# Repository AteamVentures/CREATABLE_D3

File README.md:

# CREATABLE_D3
The Perfect 3D Printer for Beginners, Educators and Experts.
[creatablelabs.com](http://creatablelabs.com/)

## Open Source Hardware
This product is certified open source hardware. 
[https://certification.oshwa.org/kr000001.html](https://certification.oshwa.org/kr000001.html)

#### Folder Description
 - Hardware : Mainboard, OLED board, Heat bed circuit board and PCB file (The mainboard is working with Allegro of Cadence and the rest is working with Eagle CAD)
 - Firmware : Mainboard firmware [Download](https://github.com/AteamVentures/CREATABLE_D3/raw/master/Firmware/D3_Firmware.zip)  
	1. Connect the printer and computer with the USB cable.
	2. Unzip the file you received from the link above.
	3. Run Cue and execute Machine> Install Custom Firmware ... from the main menu.
	4. Select the hex file from step 2 and click Open.
	5. Wait for uploading to finish.
	6. After completing the upload, operate the printer's menu to execute INFO / SETTINGS> RESTORE DEFAULT.
	7. Execute the leveling and filament insertion according to the first run instructions. If you have already done so, continue to press the button without further action.
	8. Execute INFO / SETTINGS> FIRMWARE VERSION to check the version information.

 - stk500v2 : This it the ATmega2560 bootloader of main board.

#### Cura CREATABLE Edition

- To use the printer, a slicing process is required to convert model files (stl, obj, etc.) to Gcode. To do this, we offer Cura CREATABLE Edition, a slicing software.
- Information on the Cura CREATABLE Edition can be found at the following link.
- [Cura CREATABLE Edition](https://github.com/AteamVentures/CuraCreatableEdition)

#### Folder Description
 -  Hardware: Mainboard, OLED board, Heat bed circuit board and PCB file (The mainboard is working with Cadence's Allegro and the rest with Eagle CAD)
 - Firmware : Mainboard firmware [Download](https://github.com/AteamVentures/CREATABLE_D3/raw/master/Firmware/D3_Firmware.zip)  
	#### How to update firmare
	1. Connect the printer and computer with a USB cable.
	2. Unzip the file you received from the link above.
	3. Execute Cura and run Machine> Install Custom Firmware ... from the main menu.
	4. Select the hex file from step 2 and click "Open".
	5. Wait for uploading to finish.
	6. After completing the upload, operate the printer's menu to execute INFO / SETTINGS> RESTORE DEFAULT.
	7. Execute leveling and filament insertion according to "First run" instructions. If you have already done so, continue to press the button without further action.
	8. Execute INFO / SETTINGS> FIRMWARE VERSION to check the version information.
	- stk500v2 : 메인 보드 ATmega2560 bootloader

#### Differences from Creatable D2 in H/W

- Using Silab's CP2104 for USB connection
- Motor driver A4988 is onboard.
- OLED board: Integrate 2 boards into one board
- Heat bed: Adjusts the resistance value so that it is heated quickly.

#### Cura CREATABLE Edition

- To use the printer, a slicing process is required to convert model files (stl, obj, etc.) into Gcode. To do this, we offer Cura CREATABLE Edition (Cutomized Cura).
- Information about the Cura CREATABLE Edition can be found at the following link.
- [Cura CREATABLE Edition Link](https://github.com/AteamVentures/CuraCreatableEdition)

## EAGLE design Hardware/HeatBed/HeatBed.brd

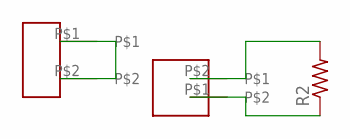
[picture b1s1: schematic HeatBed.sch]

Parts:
R2: R-US_R0402; R0402
U$2: SMD_WAFER_2; SMD_WAFER_02
U$3: SMD_TERMINAL_2; SMD_5MM_2

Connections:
unnamed: R2.2, U$2.P$2
unnamed: R2.1, U$2.P$1
unnamed: U$3.P$1, U$3.P$2

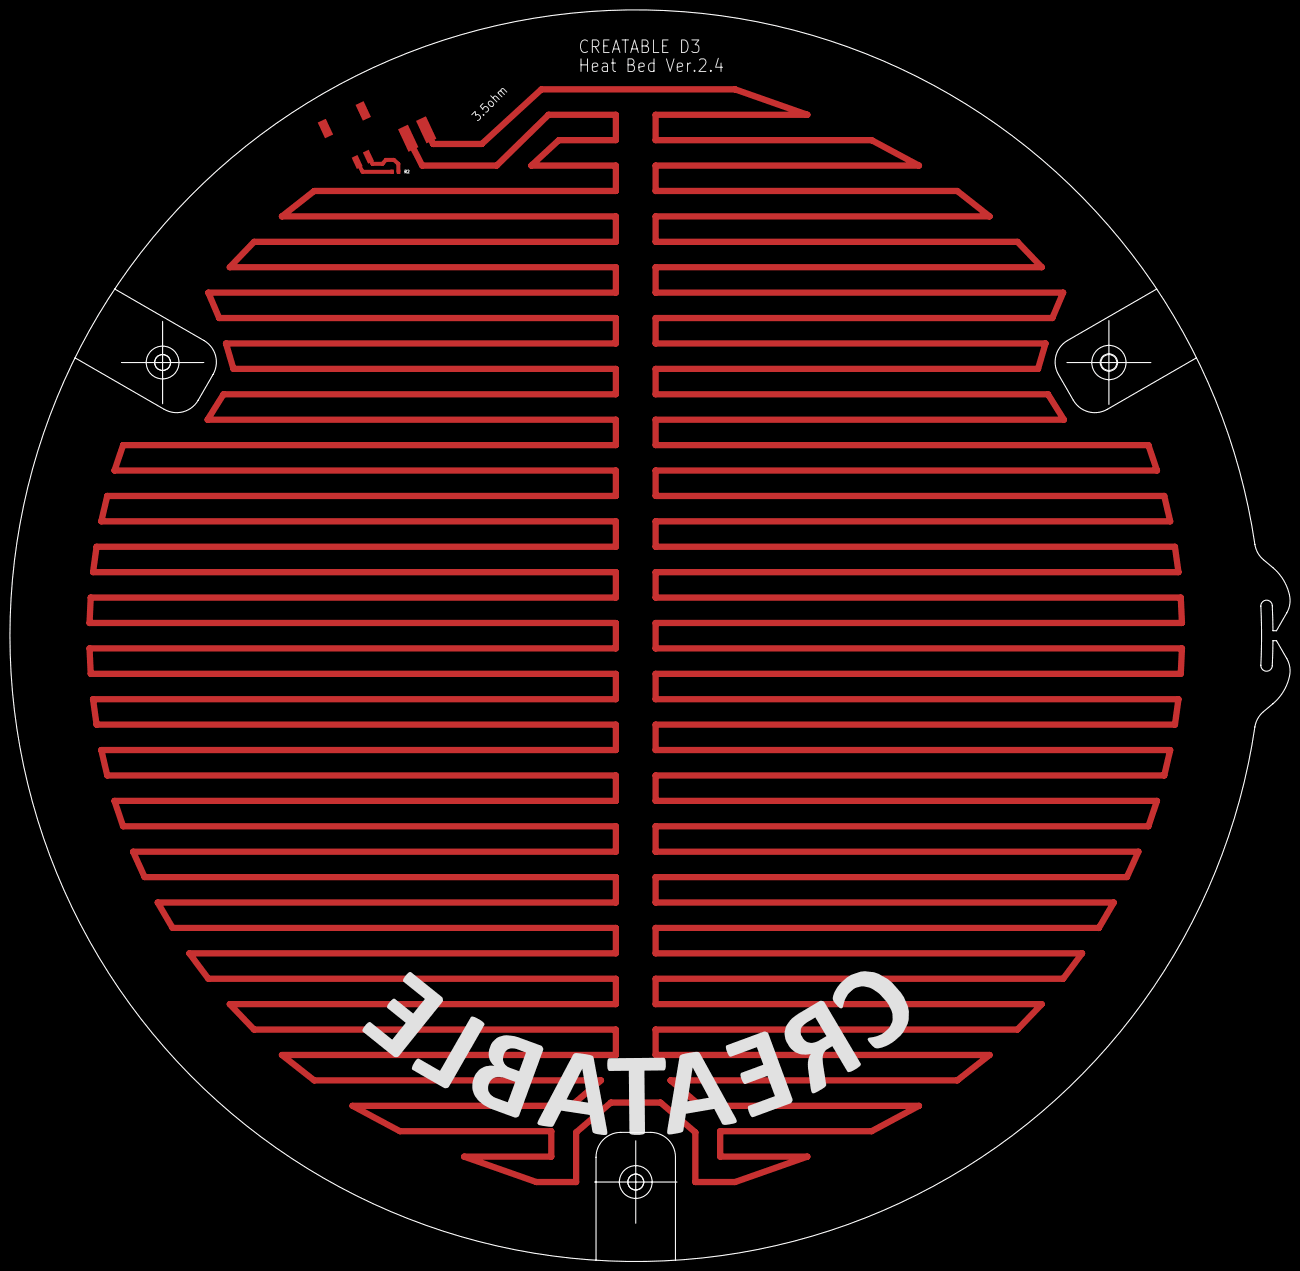
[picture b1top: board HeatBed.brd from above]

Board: 2 copper layers, 257.7 x 252.0 mm, 5 parts (1 on the bottom side), 3 nets.

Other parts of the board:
U$1: HEAT_BED2.3(R126_T2.3)
U$4: CREATABLE_WORD

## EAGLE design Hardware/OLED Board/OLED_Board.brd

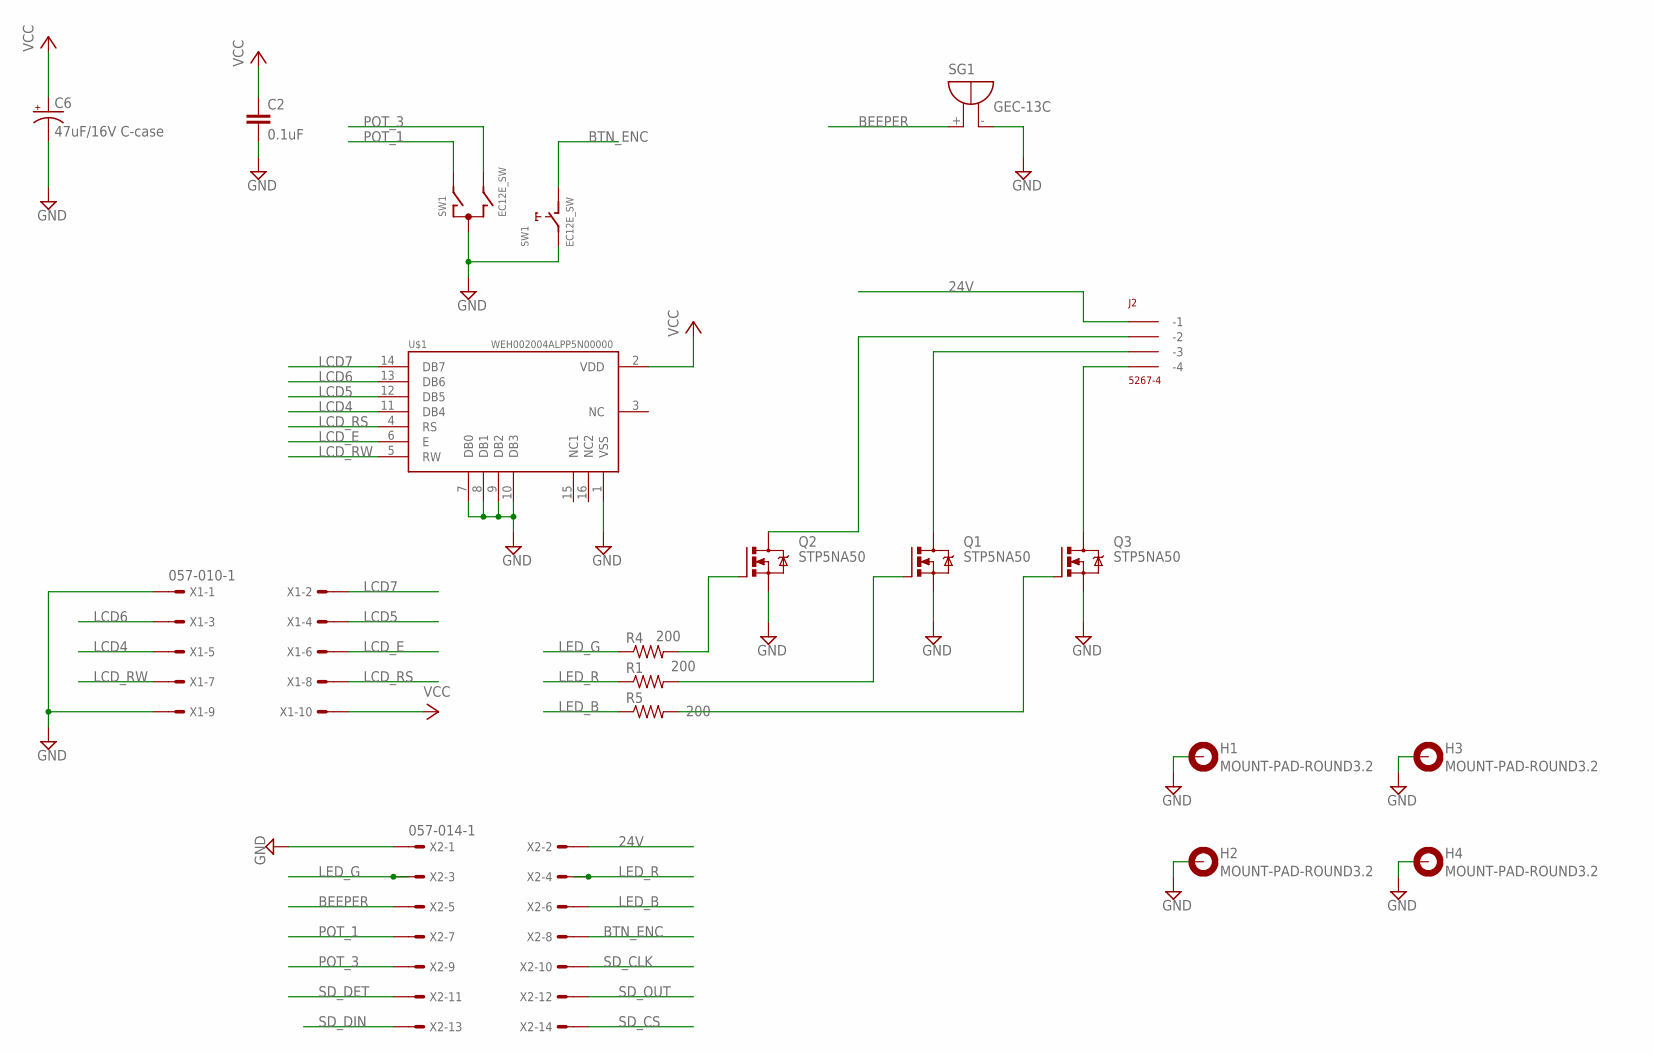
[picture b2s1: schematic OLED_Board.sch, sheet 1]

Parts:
C2: 0.1uF; C0805
C6: 47uF/16V C-case; EIA6032
H1, H2, H3, H4: MOUNT-PAD-ROUND3.2; 3,2-PAD
J2: 5267-4
Q1, Q2, Q3: STP5NA50; TO220BV
R1, R4, R5: 200; R2012
SG1: GEC-13C; F/TMB
SW1: EC12E_SW; ALPS_EC12E_SW
U$1: OLED; WEH002004ALPP5N00000
X1: 057-010-1
X2: 057-014-1

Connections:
24V: J2.P$1 (-1), X2.2
BEEPER: SG1.+, X2.5
BTN_ENC: SW1.D (1), X2.8
GND: C2.2, C6.P$2 (-), H1.B3,2, H2.B3,2, H3.B3,2, H4.B3,2, Q1.S, Q2.S, Q3.S, SG1.-, SW1.C, SW1.E (2), U$1.1 (VSS), U$1.7 (DB0), U$1.8 (DB1), U$1.9 (DB2), U$1.10 (DB3), X1.1, X1.9, X2.1; also elsewhere on the board
LCD4: U$1.11 (DB4), X1.5
LCD5: U$1.12 (DB5), X1.4
LCD6: U$1.13 (DB6), X1.3
LCD7: U$1.14 (DB7), X1.2
LCD_E: U$1.6 (E), X1.6
LCD_RS: U$1.4 (RS), X1.8
LCD_RW: U$1.5 (RW), X1.7
LED_B: R5.1, X2.6
LED_G: R4.1, X2.3
LED_R: R1.1, X2.4
unnamed: Q2.G, R4.2
unnamed: Q1.G, R1.2
unnamed: Q3.G, R5.2
unnamed: J2.P$2 (-2), Q2.D
unnamed: J2.P$3 (-3), Q1.D
unnamed: J2.P$4 (-4), Q3.D
POT_1: SW1.A, X2.7
POT_3: SW1.B, X2.9
SD_CLK: X2.10; also elsewhere on the board
SD_CS: X2.14; also elsewhere on the board
SD_DET: X2.11; also elsewhere on the board
SD_DIN: X2.13; also elsewhere on the board
SD_OUT: X2.12; also elsewhere on the board
VCC: C2.1, C6.P$1 (+), U$1.2 (VDD), X1.10; also elsewhere on the board

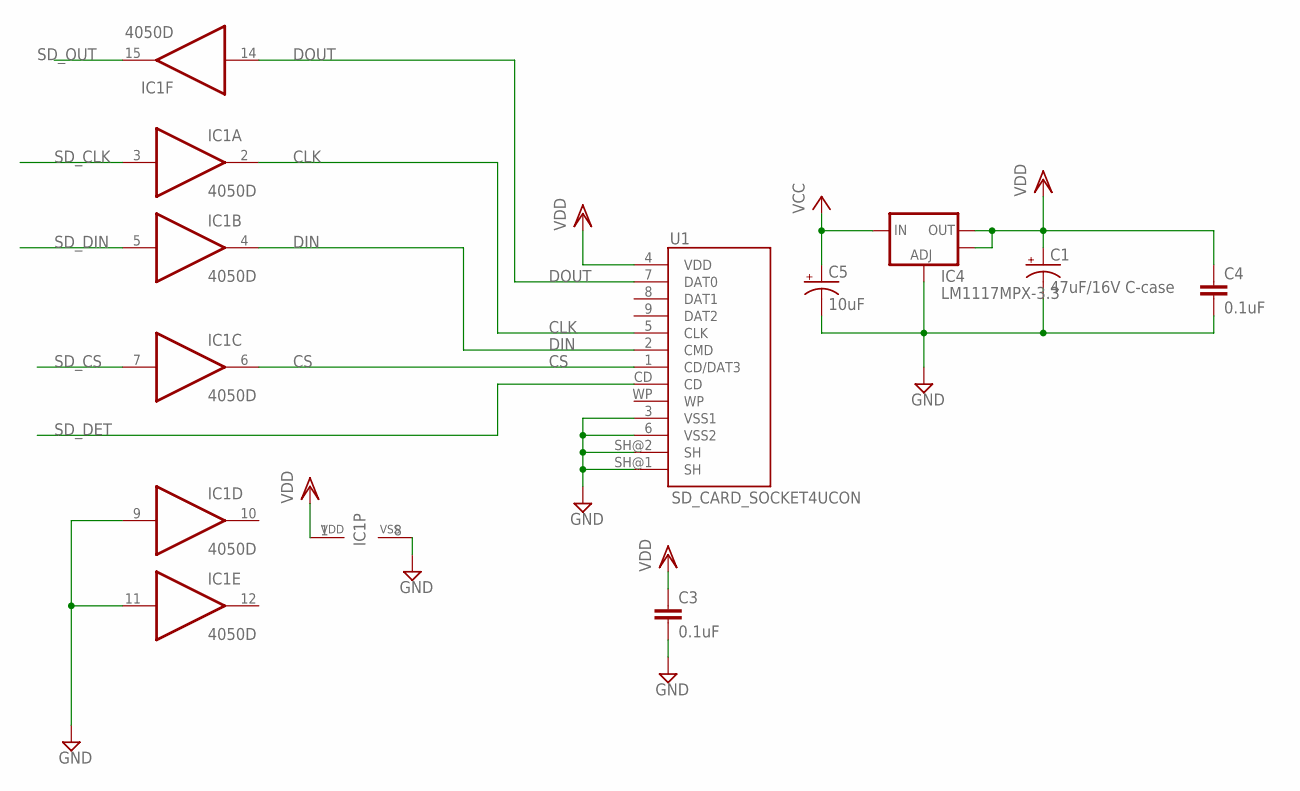
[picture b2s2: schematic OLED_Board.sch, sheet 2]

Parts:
C1: 47uF/16V C-case; EIA6032
C3, C4: 0.1uF; C0805
C5: 10uF; CT3216
IC1: 4050D; SO16
IC4: LM1117MPX-3.3; SOT223
U1: SD_CARD_SOCKET4UCON; SDCARD_4UCONN

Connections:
CLK: IC1.2 (O), U1.5 (CLK)
CS: IC1.6 (O), U1.1 (CD/DAT3)
DIN: IC1.4 (O), U1.2 (CMD)
DOUT: IC1.14 (I), U1.7 (DAT0)
GND: C1.P$2 (-), C3.2, C4.2, C5.-, IC1.8 (VSS), IC1.9 (I), IC1.11 (I), IC4.1 (ADJ), U1.3 (VSS1), U1.6 (VSS2), U1.SH@1 (SH), U1.SH@2 (SH); also elsewhere on the board
SD_CLK: IC1.3 (I); also elsewhere on the board
SD_CS: IC1.7 (I); also elsewhere on the board
SD_DET: U1.CD; also elsewhere on the board
SD_DIN: IC1.5 (I); also elsewhere on the board
SD_OUT: IC1.15 (O); also elsewhere on the board
VCC: C5.+, IC4.3 (IN); also elsewhere on the board
VDD: C1.P$1 (+), C3.1, C4.1, IC1.1 (VDD), IC4.2 (OUT), IC4.4 (OUT), U1.4 (VDD)

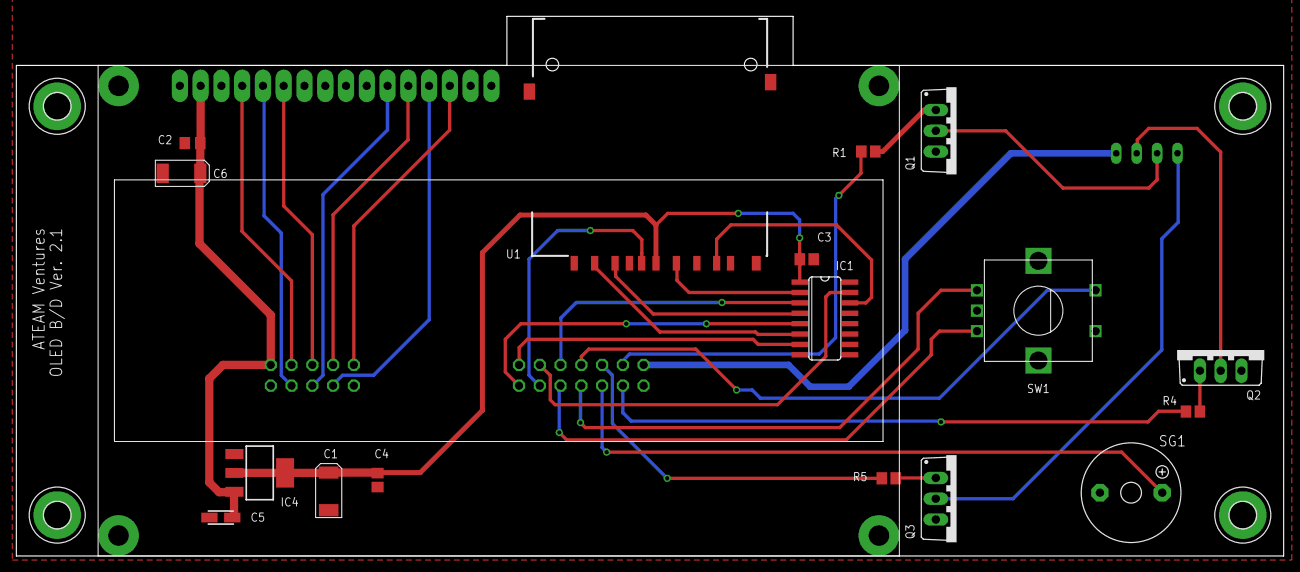
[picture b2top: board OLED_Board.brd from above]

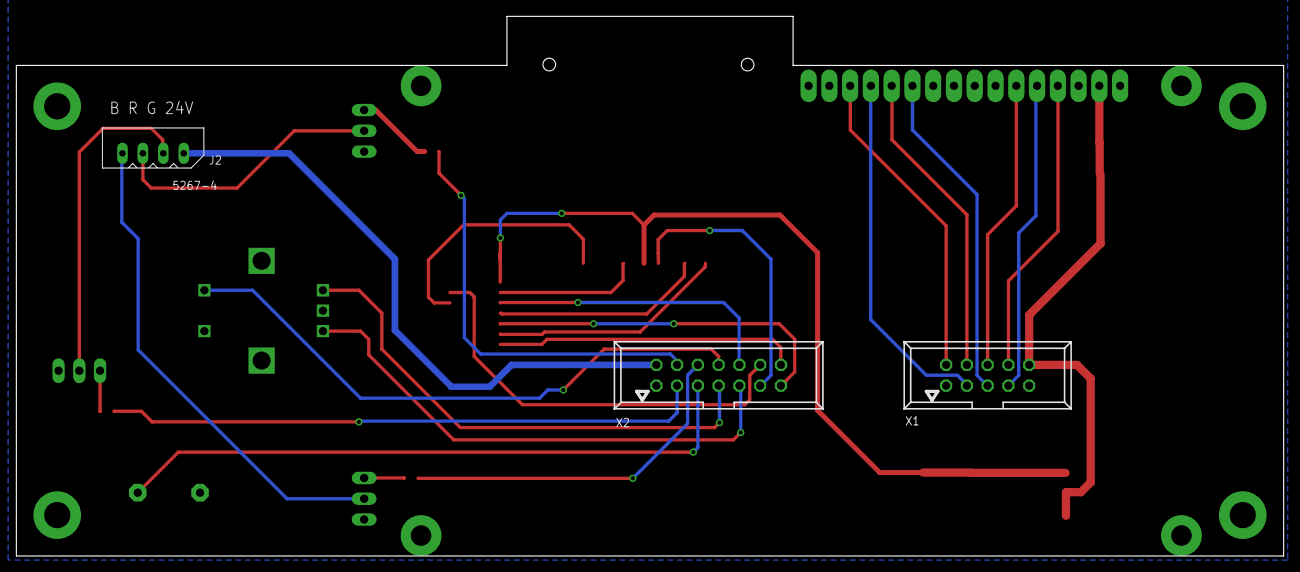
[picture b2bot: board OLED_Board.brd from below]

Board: 2 copper layers, 155.0 x 66.0 mm, 25 parts (3 on the bottom side), 33 nets.

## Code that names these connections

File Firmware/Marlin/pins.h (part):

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    //#define TX_ENABLE_PIN       12
    //#define RX_ENABLE_PIN       13

    #define BEEPER -1
    #define SDCARDDETECT -1
    #define SUICIDE_PIN -1    //has to be defined; otherwise Power_off doesn't work

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     //buttons are directly attached
    #define BTN_EN1 11
    #define BTN_EN2 10
    #define BTN_ENC 12  //the click

#endif

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    #define SDSS               25//53
    #define LED_PIN            13

    #define BEEPER             33

  #else

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  #endif

  #if MOTHERBOARD == 68
    #define BEEPER 33
  #endif

  #ifdef TEMP_STAT_LEDS
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      #define LCD_PINS_D7 29

      #ifdef REPRAP_DISCOUNT_SMART_CONTROLLER
        #define BEEPER 37

        #define BTN_EN1 31
        #define BTN_EN2 33
        #define BTN_ENC 35

        #define SDCARDDETECT 49
      #elif defined(LCD_I2C_PANELOLU2)
        #define BTN_EN1 47  //reverse if the encoder turns the wrong way.
        #define BTN_EN2 43
        #define BTN_ENC 32
        #define SDSS 53
        #define SDCARDDETECT -1
        #define KILL_PIN 41
      #elif defined(LCD_I2C_VIKI)
        #define BTN_EN1 22  //reverse if the encoder turns the wrong way.
        #define BTN_EN2 7
        #define BTN_ENC -1
        #define SDSS 53
        #define SDCARDDETECT 49
      #else
        //arduino pin which triggers an piezzo beeper
        #define BEEPER 33  // Beeper on AUX-4

        //buttons are directly attached using AUX-2
        #ifdef REPRAPWORLD_KEYPAD
          #define BTN_EN1 64 // encoder
          #define BTN_EN2 59 // encoder
          #define BTN_ENC 63 // enter button
          #define SHIFT_OUT 40 // shift register
          #define SHIFT_CLK 44 // shift register
          #define SHIFT_LD 42 // shift register
        #else
          #define BTN_EN1 37
          #define BTN_EN2 35
          #define BTN_ENC 31  //the click
        #endif

        #ifdef G3D_PANEL
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      #endif

      #if MOTHERBOARD == 77
        #define BEEPER -1

        #define LCD_PINS_RS 27
        #define LCD_PINS_ENABLE 29
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       //buttons
       #define BTN_EN1 16
       #define BTN_EN2 17
       #define BTN_ENC 23 //the click

    #endif
    #else //old style panel with shift register
      //arduino pin witch triggers an piezzo beeper
      #define BEEPER 33		//No Beeper added

      //buttons are attached to a shift register
	// Not wired this yet
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#define TEMP_2_PIN         1 	//ANALOG NUMBERING
#define TEMP_BED_PIN       0	//ANALOG NUMBERING

#define BEEPER 		         36

#define KILL_PIN           -1

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
  #define BTN_EN1          14
  #define BTN_EN2          39
  #define BTN_ENC          15  //the click

  #define BLEN_C           2
  #define BLEN_B           1
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 #ifdef ULTRA_LCD
   #ifdef NEWPANEL
     //we have no buzzer installed
     #define BEEPER -1
     //LCD Pins
     #ifdef DOGLCD
       // Pins for DOGM SPI LCD Support
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     #define BTN_EN2 10
     #ifdef LCD_I2C_PANELOLU2
       #ifdef MELZI
         #define BTN_ENC 29 //the click switch
         #define SDSS 30 //to use the SD card reader on the Panelolu2 rather than the melzi board
       #else
         #define BTN_ENC 30 //the click switch
       #endif
     #else
       #define BTN_ENC 16  //the click switch
     #endif //Panelolu2
     //not connected to a pin
     #define SDCARDDETECT -1
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 #endif //Ultipanel

 #ifdef MAKRPANEL
     #define BEEPER 29
     // Pins for DOGM SPI LCD Support
     #define DOGLCD_A0  30
     #define DOGLCD_CS  17
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     //The encoder and click button
     #define BTN_EN1 11
     #define BTN_EN2 10
     #define BTN_ENC 16  //the click switch
     //not connected to a pin
     #define SDCARDDETECT -1
 #endif //Makrpanel
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#ifdef ULTRA_LCD

  #ifdef NEWPANEL
  //arduino pin witch triggers an piezzo beeper
    #define BEEPER 18

    #define LCD_PINS_RS 20
    #define LCD_PINS_ENABLE 17
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    //buttons are directly attached
    #define BTN_EN1 40
    #define BTN_EN2 42
    #define BTN_ENC 19  //the click

    #define SDCARDDETECT 38

  #else //old style panel with shift register
    //arduino pin witch triggers an piezzo beeper
    #define BEEPER 18

    //buttons are attached to a shift register
    #define SHIFT_CLK 38
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#define MOTOR_CURRENT_PWM_RANGE 2000
#define DEFAULT_PWM_MOTOR_CURRENT  {1300, 1300, 1250}

//arduino pin witch triggers an piezzo beeper
#define BEEPER 18

#define LCD_PINS_RS 20
#define LCD_PINS_ENABLE 15
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//buttons are directly attached
#define BTN_EN1 40
#define BTN_EN2 41
#define BTN_ENC 19  //the click

#define BLEN_C 2
#define BLEN_B 1
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#define SDPOWER            -1
#define SDSS               53
#define SDCARDDETECT       49
#define BEEPER             44
#define LCD_PINS_RS        19
#define LCD_PINS_ENABLE    42
#define LCD_PINS_D4        18
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#define LCD_PINS_D7        40
#define BTN_EN1            11
#define BTN_EN2            12
#define BTN_ENC            43

// added for OLED
#define LCD_PINS_RW        46
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#define IN1    14
*/
// LED strip
#define LED_R       6// old version(none pwm) pin is 21
#define LED_G       8// old version(none pwm) pin is 20
#define LED_B       4
#define LED_R_NONE_PWM 21
#define LED_G_NONE_PWM 20

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#if 0
#ifdef BOARD_VER1_2
// LED strip
#define LED_R       6// old version(none pwm) pin is 21
#define LED_G       8// old version(none pwm) pin is 20
#define LED_B       4

#else

#define LED_R       21
#define LED_G       20
#define LED_B       4

#endif
#endif
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  #define MOSI_PIN         10
#endif

#define BEEPER             -1
#define LCD_PINS_RS        -1
#define LCD_PINS_ENABLE    -1
#define LCD_PINS_D4        -1
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#define LCD_PINS_D7        -1
#define BTN_EN1            -1
#define BTN_EN2            -1
#define BTN_ENC            -1

// For LCD SHIFT register LCD
#define SR_DATA_PIN         0
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#ifdef ULTRA_LCD
  #define KILL_PIN 80
  #ifdef NEWPANEL
   //arduino pin which triggers an piezzo beeper
    #define BEEPER 79      // Beeper on AUX-4
    #define LCD_PINS_RS 70
    #define LCD_PINS_ENABLE 71
    #define LCD_PINS_D4 72
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    //buttons are directly attached using AUX-2
    #define BTN_EN1 76
    #define BTN_EN2 77
    #define BTN_ENC 78  //the click

    #define BLEN_C 2
    #define BLEN_B 1
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    #define encrot2 3
    #define encrot3 1
  #else //old style panel with shift register
    //arduino pin witch triggers an piezzo beeper
    #define BEEPER 33    No Beeper added
    //buttons are attached to a shift register
    // Not wired this yet
    // #define SHIFT_CLK 38
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#define HEATER_BED_PIN     10   // BED
#define TEMP_BED_PIN       14   // ANALOG NUMBERING

#define BEEPER 33     // Beeper on AUX-4


#ifdef ULTRA_LCD

  #ifdef NEWPANEL
  //arduino pin which triggers an piezzo beeper

    #define LCD_PINS_RS 16
    #define LCD_PINS_ENABLE 17
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    //buttons are directly attached using AUX-2
    #define BTN_EN1 59
    #define BTN_EN2 64
    #define BTN_ENC 43  //the click

    #define BLEN_C 2
    #define BLEN_B 1
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   #define TEMP_BED_PIN 14 // ANALOG NUMBERING
 #endif

 #define BEEPER 64


 #define LCD_PINS_RS 14
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 //buttons are directly attached using keypad
 #define BTN_EN1 61
 #define BTN_EN2 59
 #define BTN_ENC 43 //the click

 #define BLEN_C 2
 #define BLEN_B 1
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 #define HEATER_BED_PIN 3 // BED
 #define TEMP_BED_PIN 6 // ANALOG NUMBERING

 #define BEEPER -1


 #define LCD_PINS_RS -1
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 //buttons are directly attached using keypad
 #define BTN_EN1 -1
 #define BTN_EN2 -1
 #define BTN_ENC -1 //the click

 #define BLEN_C 2
 #define BLEN_B 1
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 //Cheaptronic v1.0 dont support keypad
 #define BTN_EN1 -1
 #define BTN_EN2 -1
 #define BTN_ENC -1

 #define BLEN_C 2
 #define BLEN_B 1
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
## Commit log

2016-07-15 1st commit
2016-07-15 CREATABLE D3 Firmware Ver.1.0.4
    Ver. 1.0.4
    -. Apply 3 point manual leveling
    -. Add LED control
    -. Add Buzzer on/off
2016-07-19 Version 1.0.5 Update
    Ver. 1.0.5
    -. While SD Card Printing, stepper deactivate time is changed from 60
    to 9999 seconds.
2016-07-20 Version 1.0.6
    - Delete D2 firmware files
    - Change Delta Radius Values in configuration.h file
    - Add D3 Delta Radius Values image
2016-07-20 Change Version Notification Method
2016-07-20 Version Name Update
2016-07-21 Ver. 1.0.7
    -. Filament load function debug
    -. Enable/Disable Unlimit Heating Code add
    -. V130 : Enable Unlimit Heating
    -. V131 : Disable Unlimit Heating
    -. Change wording (Select Filament)
2016-07-21 Disable Autoleveling
2016-07-21 Ver. 1.0.8
    -. Change DEFAULT_AXIS_STEPS_PER_UNIT Constant for feeder in
    Configuration.h
    -. Auto Leveling Code is Disabled
2016-08-10 Ver.1.0.9
2016-08-10 Add Hex file 1.0.9
2016-08-25 Ver 1.1.0 Update
    -. Comment Utilities > Clean Nozzle Function
    -. Change Manual Z Home Position from 232 to 230 for changed bed clip
2016-09-19 Compress Hex File to make download link of firmware file
2016-09-19 Firmware Update Guide Appended
2016-09-19 Edit mistypes
2016-10-10 Ver 1.1.1 Update
    -. When get serial data, reset the heat-hold-count.
    -. Change default heat-hold-time from 10 minutes to 30 minutes.
2016-10-10 FW History file change to markdown style
2016-10-10 Fix the FW file
2016-10-10 Heat Hold Time related modification
    M104 / M140 / M109 / M190
    + S{temp}
    if temp > 0 disable heathold timeout
    else if temp==0 enable heathold timeout
2016-10-10 update board coordinate file
2016-11-24 Ver. 1.1.2 Update
    - Auto fan control enable. Nozzle temperature is under 50 celcius
    degrees, fan will be turned off.
    - When get serial data, motor will be hold. Originally, motor hold time
    was 60 seconds. However, we change it to 6000 seconds.
2016-11-24 .DS_Store banished!
2016-12-07 Ver. 1.1.3
    - Change Error Temperature from 5 to -80
2016-12-29 cura info update
2017-01-03 LED pin option & Fan option defined
2017-03-06 Add English translation in README.md
2017-03-13 Ver. 1.1.5 Update
    Ver. 1.1.5
    - Supports LED pin of both mainboards(Ver 1.1 & 1.2)
    - Add Go home movement before Load / Unload Filament
2017-05-29 Ver 1.1.6 update
    - Fix the wrong retraction speed set after load the filament
2017-05-29 1.1.6 fw update
2017-07-25 Support Craftware and Repetier Host
2017-07-25 make zip for download link
2017-08-08 upload mannual
2018-10-24 Rev2. Add
2019-05-17 Add zip file
2019-07-29 Create LICENSE
2019-08-19 upload gerber

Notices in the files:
parts and their libraries:
SparkFun: Licensing: CC v3.0 Share-Alike You are welcome to use this library for commercial purposes.
SparkFun-Connectors: Licensing: Creative Commons ShareAlike 4.0 International - https://creativecommons.org/licenses/by-sa/4.0
